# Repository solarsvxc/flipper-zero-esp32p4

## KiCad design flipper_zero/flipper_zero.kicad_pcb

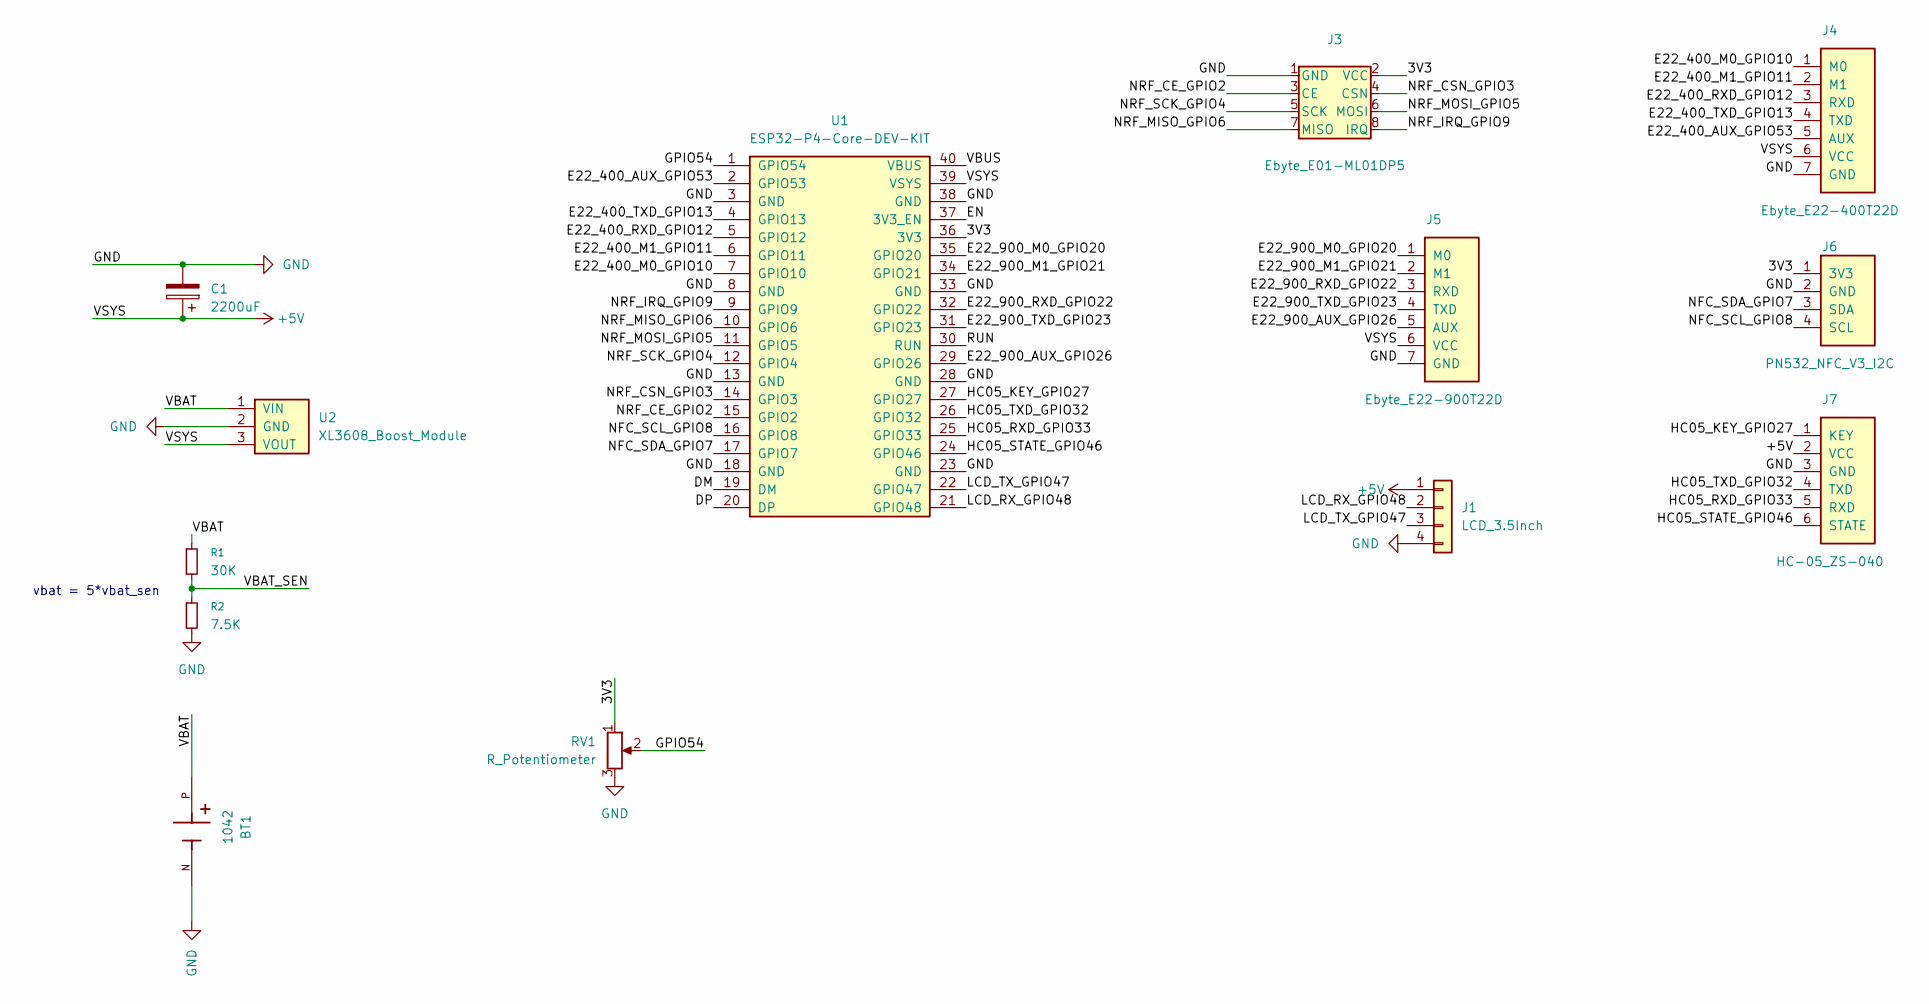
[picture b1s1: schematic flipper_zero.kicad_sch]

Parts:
BT1: 1042; 1042_17e5a930__BAT_1042; PARTREV E
C1: 2200uF; CP_Radial_D14.0mm_P5.00mm
J1: LCD_3.5Inch; JST_GH_SM04B-GHS-TB_1x04-1MP_P1.25mm_Horizontal
J3: Ebyte_E01-ML01DP5
J4: Ebyte_E22-400T22D
J5: Ebyte_E22-900T22D
J6: PN532_NFC_V3_I2C; PinSocket_1x04_P2.54mm_Vertical
J7: HC-05_ZS-040
R1: 30K; R_Axial_DIN0207_L6.3mm_D2.5mm_P7.62mm_Horizontal
R2: 7.5K; R_Axial_DIN0207_L6.3mm_D2.5mm_P7.62mm_Horizontal
RV1: R_Potentiometer; DIP-14_W7.62mm
U1: ESP32-P4-Core-DEV-KIT
U2: XL3608_Boost_Module

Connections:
+5V: C1.1, J1.1, J4.6 (VCC), J5.6 (VCC), J7.2 (VCC), U1.39 (VSYS), U2.3 (VOUT)
/3V3: J3.2 (VCC), J6.1 (3V3), RV1.1, U1.36 (3V3)
/DM: U1.19 (DM)
/DP: U1.20 (DP)
/E22_400_AUX_GPIO53: J4.5 (AUX), U1.2 (GPIO53)
/E22_400_M0_GPIO10: J4.1 (M0), U1.7 (GPIO10)
/E22_400_M1_GPIO11: J4.2 (M1), U1.6 (GPIO11)
/E22_400_RXD_GPIO12: J4.3 (RXD), U1.5 (GPIO12)
/E22_400_TXD_GPIO13: J4.4 (TXD), U1.4 (GPIO13)
/E22_900_AUX_GPIO26: J5.5 (AUX), U1.29 (GPIO26)
/E22_900_M0_GPIO20: J5.1 (M0), U1.35 (GPIO20)
/E22_900_M1_GPIO21: J5.2 (M1), U1.34 (GPIO21)
/E22_900_RXD_GPIO22: J5.3 (RXD), U1.32 (GPIO22)
/E22_900_TXD_GPIO23: J5.4 (TXD), U1.31 (GPIO23)
/EN: U1.37 (3V3_EN)
/GPIO54: RV1.2, U1.1 (GPIO54)
/HC05_KEY_GPIO27: J7.1 (KEY), U1.27 (GPIO27)
/HC05_RXD_GPIO33: J7.5 (RXD), U1.25 (GPIO33)
/HC05_STATE_GPIO46: J7.6 (STATE), U1.24 (GPIO46)
/HC05_TXD_GPIO32: J7.4 (TXD), U1.26 (GPIO32)
/LCD_RX_GPIO48: J1.2, U1.21 (GPIO48)
/LCD_TX_GPIO47: J1.3, U1.22 (GPIO47)
/NFC_SCL_GPIO8: J6.4 (SCL), U1.16 (GPIO8)
/NFC_SDA_GPIO7: J6.3 (SDA), U1.17 (GPIO7)
/NRF_CE_GPIO2: J3.3 (CE), U1.15 (GPIO2)
/NRF_CSN_GPIO3: J3.4 (CSN), U1.14 (GPIO3)
/NRF_IRQ_GPIO9: J3.8 (IRQ), U1.9 (GPIO9)
/NRF_MISO_GPIO6: J3.7 (MISO), U1.10 (GPIO6)
/NRF_MOSI_GPIO5: J3.6 (MOSI), U1.11 (GPIO5)
/NRF_SCK_GPIO4: J3.5 (SCK), U1.12 (GPIO4)
/RUN: U1.30 (RUN)
/VBAT: BT1.P, R1.1, U2.1 (VIN)
/VBAT_SEN: R1.2, R2.1
/VBUS: U1.40 (VBUS)
GND: BT1.N, C1.2, J1.4, J3.1 (GND), J4.7 (GND), J5.7 (GND), J6.2 (GND), J7.3 (GND), R2.2, RV1.3, U1.3 (GND), U1.8 (GND), U1.13 (GND), U1.18 (GND), U1.23 (GND), U1.28 (GND), U1.33 (GND), U1.38 (GND), U2.2 (GND)

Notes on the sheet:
vbat = 5*vbat_sen

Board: 2 copper layers, 12 parts (3 on the bottom side), 29 nets, no tracks yet.
